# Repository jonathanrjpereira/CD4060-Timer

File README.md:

# CD4060 Timer

The timer can be set for a time delay from 15 seconds upto 24 hours.
The time delay can be easily changed to control the state of any device connected to the output.

**Order PCB:**

## Electronic Components
| Qty | Component | Buy |
| ------------- | ------------- | ------------- |
| 1 | CD4060 |[AliExpress](http://s.click.aliexpress.com/e/kyO7qcg) |
| 1 | IC Holder |[AliExpress](http://s.click.aliexpress.com/e/cHvnfsrA) |
| 1 | 7805 Voltage Regulator |[AliExpress](http://s.click.aliexpress.com/e/b1D8MbCk) |
| 1 | 10P DIP Switch |[AliExpress](http://s.click.aliexpress.com/e/bWTOIl7K) |
| 1 | BC547 PNP Transistor |[AliExpress](http://s.click.aliexpress.com/e/bpL0Irsk) |
| 12 | 1KΩ Resistor |[AliExpress](http://s.click.aliexpress.com/e/bh4eqrQs) |
| 2 | 910KΩ Resistor |[AliExpress](http://s.click.aliexpress.com/e/bh4eqrQs) |
| 1 | 3KΩ,100KΩ,1MΩ Resistor |[AliExpress](http://s.click.aliexpress.com/e/bh4eqrQs) |
| 2 | 10MΩ Resistor |[AliExpress](http://s.click.aliexpress.com/e/bQYFOHo4) |
| 1 | 22MΩ Resistor |[AliExpress](http://s.click.aliexpress.com/e/bQYFOHo4) |
| 11 | IN4004 Diode |[AliExpress](http://s.click.aliexpress.com/e/HW1fm16) |
| 1 | Tactile Momentary Push Buttons |[AliExpress](http://s.click.aliexpress.com/e/c77Ajrpq) |
| 12 | 5mm LED |[AliExpress](http://s.click.aliexpress.com/e/wuFpLXS) |
| 1 | 100uF Capacitor |[AliExpress](http://s.click.aliexpress.com/e/c9FHzl5W) |
| 1 | 0.22uF,0.3uF Capacitor |[AliExpress](http://s.click.aliexpress.com/e/byQG0DZW) |
| 2 | 0.1uF (100nF) Capacitor |[AliExpress](http://s.click.aliexpress.com/e/byQG0DZW) |
| 1 | 3 Pin Screw Terminal |[AliExpress](http://s.click.aliexpress.com/e/bj5UNUs0) |
| 1 | 5V Relay |[AliExpress](http://s.click.aliexpress.com/e/xyrHlu8) |
| 1 | SPDT Slide Switch |[AliExpress](http://s.click.aliexpress.com/e/cDjWUvjK) |
| 1 | DPDT Slide Switch |[AliExpress](http://s.click.aliexpress.com/e/bCi1v5gk) |
| 1 | 9V Battery Holder |[AliExpress](http://s.click.aliexpress.com/e/c3jbp72Y) |
| 1 | 9V Battery |[AliExpress](http://s.click.aliexpress.com/e/bbDirGHE) |
| 1 | PCB |[AliExpress](http://s.click.aliexpress.com/e/dhgwzKY) |

| Tools | Buy |
|--|--|
|Soldering Iron|[AliExpress](http://s.click.aliexpress.com/e/E83bSJI) |
|Soldering Wire|[AliExpress](http://s.click.aliexpress.com/e/PdhB0nm) |
|Mini PCB Hand Drill + Bits|[AliExpress](http://s.click.aliexpress.com/e/b93tomjI) |

## Working
**CD4060:**

The CD4060 consists of an oscillator section and 14 ripple carry binary counter stages. The oscillator configuration allows design of RC oscillator circuits. A RESET input is provided which resets the counter to the all-0's state and disables the oscillator. The counters are reset to the zero state by a logical “1” at the reset input independent of clock. The counters are advanced one count on the negative transition of each clock pulse.

**Timing Cycle:**

R2 must satisfy the following equation: 

where n is the Output Number i.e. 

where 2.2 is the internal propagation delay.

## Circuit

The Timer IC requires the external RC network to be preconfigured in order to generate proper timing oscillations. External resets may be used to reset the timer. The time selector is configured to change the RC network value. The high power appliances are turned on when the relay is activated.

**Resistor Calculation:**

The table below shows the timing cycle of each output calculated by using the formulae given above.

We can see that if we choose the value of R1 to be 1.9MΩ, we can obtain an output that varies from 14.79≈15sec to 4hr.

Similarly if we choose R1 to be 10.9MΩ, we obtain an output that varies from 1.4min to 24hr.

I wrote a small [Python script](https://github.com/jonathanrjpereira/CD4060-Timer/blob/master/time.py) to calculate the time delay for various resistance values including 1.9MΩ and 10MΩ.

As shown in the Resistor Calculation chart, we can get different time delays from the same output pins by simply changing the value of R. But we must also satisfy this equation  as explained earlier.

From this equation, we learn that if R = 1.9MΩ (1MΩ + 910KΩ), we must connect a suitable resistance of approximately 3.8MΩ-19MΩ to pin 11. Similarly if
R = 10.9MΩ (10MΩ + 910KΩ), we must connect a suitable resistance of approximately 21.8MΩ-109MΩ to pin 11. Hence we have chosen standard resistor values of 10MΩ and 22MΩ respectively.

We use a DPDT switch to toggle between these two resistor combinations. Note that the value of Cx i.e C5 is a constant 0.22uF and does not change by toggling the switch.

A 10-pin DIP switch is used to select a single output pin and connect it to the relay. Hence only when this pin goes HIGH, will the relay get activated.

C4 and R12 reset the timer when the circuit is turned ON through switch S4. The circuit can be reset (while being ON) by pressing the momentary switch S2.

The 7805 regulates the supply voltage from a 9V/12V source and LED11 indicates that the circuit is turned ON.

High power loads can be connected to the relays output terminals J1. When the relay is not activated, the Common(COM) terminal is connected to Normally Closed(NC) terminal. But when the relay is activated, the Common(COM) terminal is connected to Normally Open(NO) terminal. LED12 is used to indicate whether the relay has been activated.

Transistor T1 acts as a switch an ensures sufficient drive current is provided to the relay. Diode D11 acts as a flyback diode which protects the transistor T1 from voltage spikes caused by the relay coil.

Capacitor's C1, C2 & C3 are used to filter noise in the supply line.

You can **Order the PCB:** 

Or you can printout the [PDF file](https://github.com/jonathanrjpereira/CD4060-Timer/blob/master/img/printable.pdf) and make your own PCB using the [Iron-on method]().

## Contributing🛠
Are you an engineer or hobbyist who has a great idea for a new feature in this project? Maybe you have a good idea for a bug fix? Feel free to grab our code & schematics from Github and tinker with it. Don't forget to smash ⭐️ & the Pull Request button.

[![alt text][1.1]][1] [![alt text][2.1]][2] [![alt text][3.1]][3]

[1.1]: https://github.com/jonathanrjpereira/Social-Media-README/blob/master/youtube.png (YouTube)
[2.1]: https://github.com/jonathanrjpereira/Social-Media-README/blob/master/instagram.png (Instagram)
[3.1]: https://github.com/jonathanrjpereira/Social-Media-README/blob/master/github.png (GitHub)

[1]: https://www.youtube.com/channel/UCRW-41O1vy98KKgJRQoYzdg
[2]: https://www.instagram.com/electroguruji/
[3]: https://github.com/jonathanrjpereira

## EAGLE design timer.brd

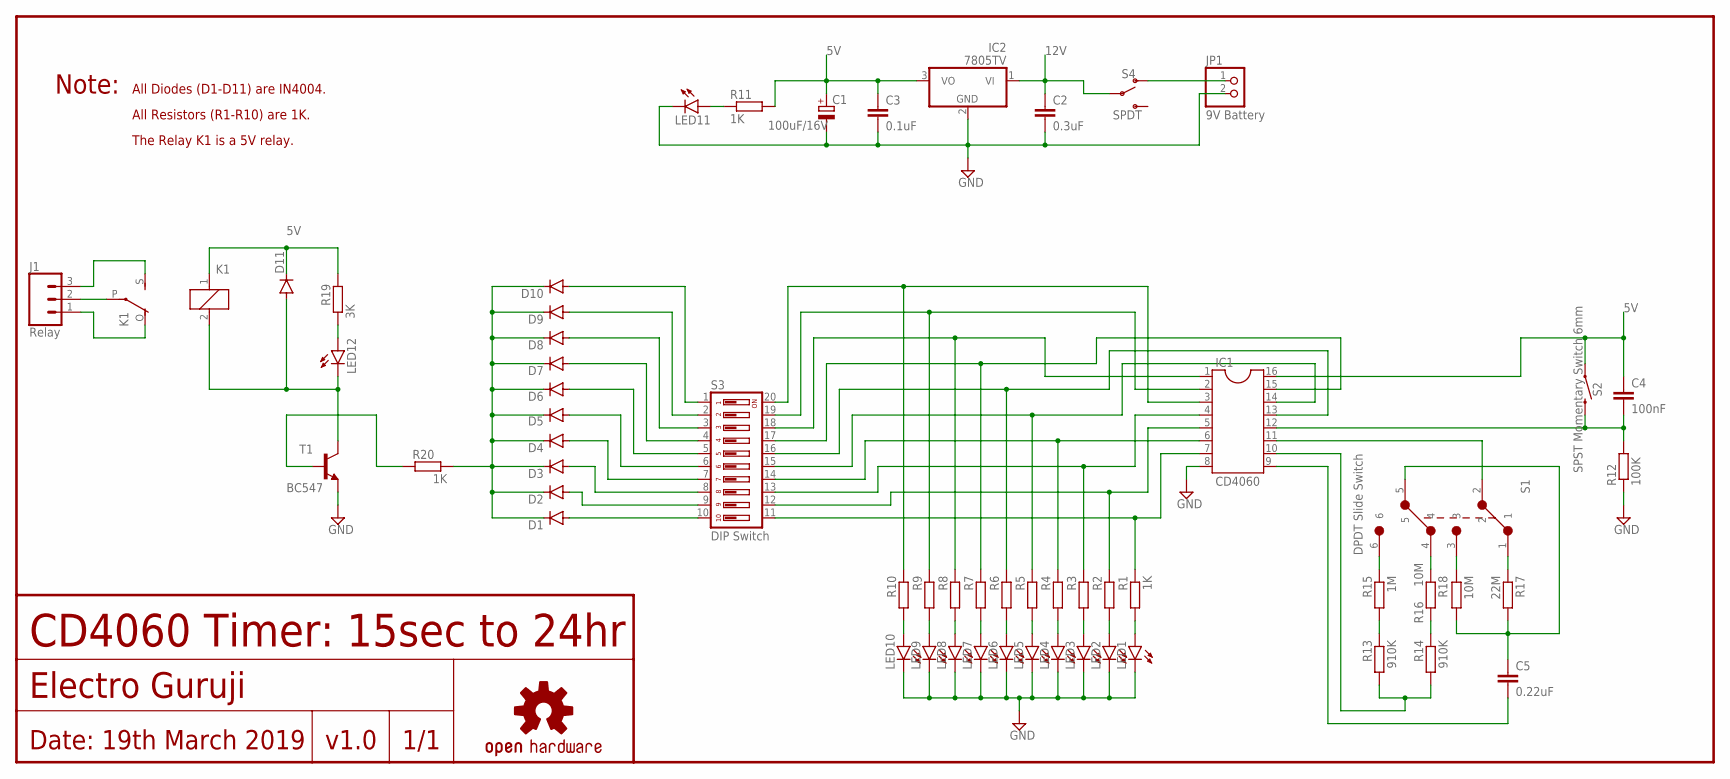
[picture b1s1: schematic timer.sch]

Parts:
C1: 100uF/16V; E2,5-6
C2: 0.3uF; C025-050X050
C3: 0.1uF; C025-050X050
C4: 100nF; C025-050X050
C5: 0.22uF; C102-043X133
D1, D2, D3, D4, D5, D6, D7, D8, D9, D10, D11: 1N4004; DO41-10
IC1: CD4060; SOCKET-16
IC2: 7805TV; TO220V
J1: Relay; SCREWTERMINAL-5MM-3
JP1: 9V Battery; 1X02
K1: 5V; ZF112
LED1, LED2, LED3, LED4, LED5, LED6, LED7, LED8, LED9, LED10, LED11, LED12: LED5MM
LOGO1: OSHW-LOGOS-COPPER; OSHW-LOGO-S_COPPER
R1, R11, R20: 1K; 0207/10
R2, R3, R4, R5, R6, R7, R8, R9, R10: R-EU_0207/10; 0207/10
R12: 100K; 0207/10
R13, R14: 910K; 0207/10
R15: 1M; 0207/10
R16, R18: 10M; 0207/10
R17: 22M; 0207/10
R19: 3K; 0207/10
S1: DPDT Slide Switch; DPDT_SEC
S2: SPST Momentary Switch 6mm; TACTILE_SWITCH_PTH_6.0MM
S3: DIP Switch; DIP10YL
S4: SPDT; SWITCH_SPDT_PTH_11.6X4.0MM
T1: BC547; TO92-EBC

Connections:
5V: C1.+, C3.1, C4.1, D11.C, IC1.16, IC2.3 (VO), K1.1, R11.2, R19.2, S2.1
12V: C2.1, IC2.1 (VI), S4.2
GND: C1.-, C2.2, C3.2, IC1.8, IC2.2 (GND), JP1.2, LED1.K (C), LED2.K (C), LED3.K (C), LED4.K (C), LED5.K (C), LED6.K (C), LED7.K (C), LED8.K (C), LED9.K (C), LED10.K (C), LED11.K (C), R12.1, T1.E
unnamed: C4.2, IC1.12, R12.2, S2.3 (2)
unnamed: LED11.A, R11.1
unnamed: IC1.10, R13.2, R14.2
unnamed: IC1.7, R1.1, S3.11
unnamed: R13.1, R15.2
unnamed: R14.1, R16.2
unnamed: C5.1, R17.2, R18.2, S1.5
unnamed: R18.1, S1.3
unnamed: R17.1, S1.1
unnamed: R16.1, S1.4
unnamed: R15.1, S1.6
unnamed: IC1.11, S1.2
unnamed: C5.2, IC1.9
unnamed: D1.A, S3.10
unnamed: IC1.5, R2.1, S3.12
unnamed: IC1.4, R3.1, S3.13
unnamed: IC1.6, R4.1, S3.14
unnamed: IC1.14, R5.1, S3.15
unnamed: IC1.13, R6.1, S3.16
unnamed: IC1.15, R7.1, S3.17
unnamed: IC1.1, R8.1, S3.18
unnamed: IC1.2, R9.1, S3.19
unnamed: IC1.3, R10.1, S3.20
unnamed: D2.A, S3.9
unnamed: D3.A, S3.8
unnamed: D4.A, S3.7
unnamed: D5.A, S3.6
unnamed: D6.A, S3.5
unnamed: D7.A, S3.4
unnamed: D8.A, S3.3
unnamed: D9.A, S3.2
unnamed: D10.A, S3.1
unnamed: LED10.A, R10.2
unnamed: LED9.A, R9.2
unnamed: LED8.A, R8.2
unnamed: LED7.A, R7.2
unnamed: LED6.A, R6.2
unnamed: LED5.A, R5.2
unnamed: LED4.A, R4.2
unnamed: LED3.A, R3.2
unnamed: LED2.A, R2.2
unnamed: LED1.A, R1.2
unnamed: R20.2, T1.B
unnamed: D11.A, K1.2, LED12.K (C), T1.C
unnamed: LED12.A, R19.1
unnamed: J1.2, K1.P
unnamed: J1.3, K1.S
unnamed: J1.1, K1.O
unnamed: JP1.1, S4.1 (O)
unnamed: D1.C, D2.C, D3.C, D4.C, D5.C, D6.C, D7.C, D8.C, D9.C, D10.C, R20.1

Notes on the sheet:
Note:
All Diodes (D1-D11) are IN4004.
All Resistors (R1-R10) are 1K.
The Relay K1 is a 5V relay.
CD4060 Timer: 15sec to 24hr
Electro Guruji
Date: 19th March 2019
v1.0
1/1

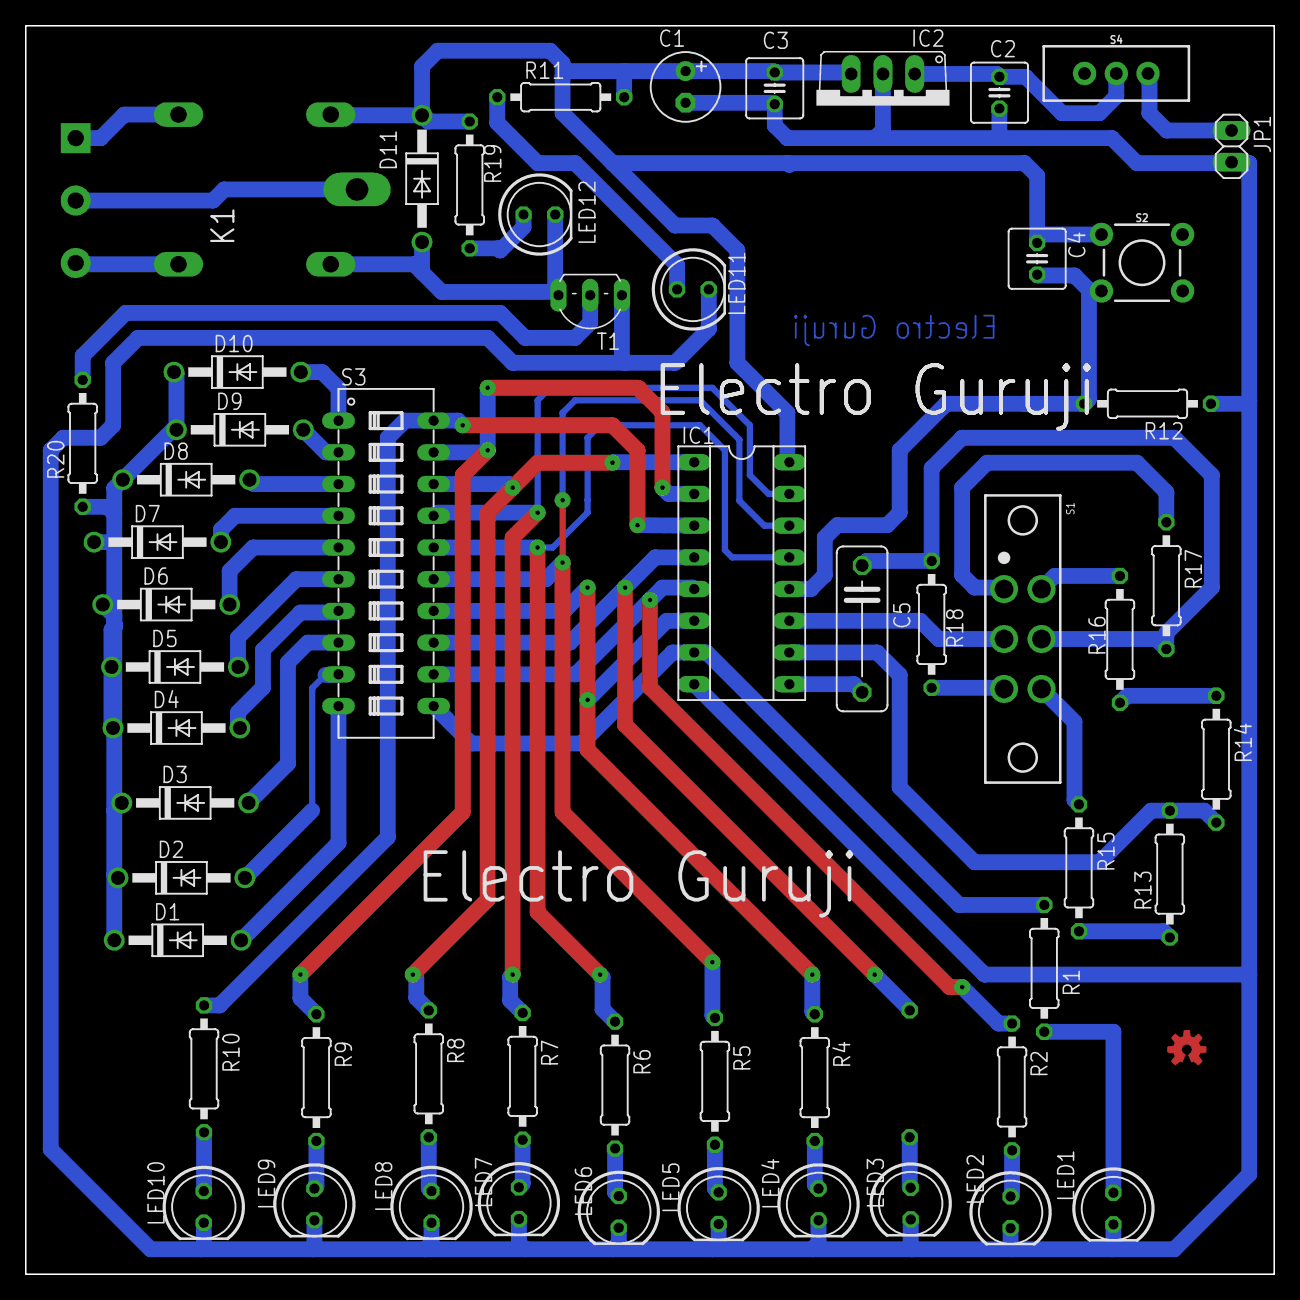
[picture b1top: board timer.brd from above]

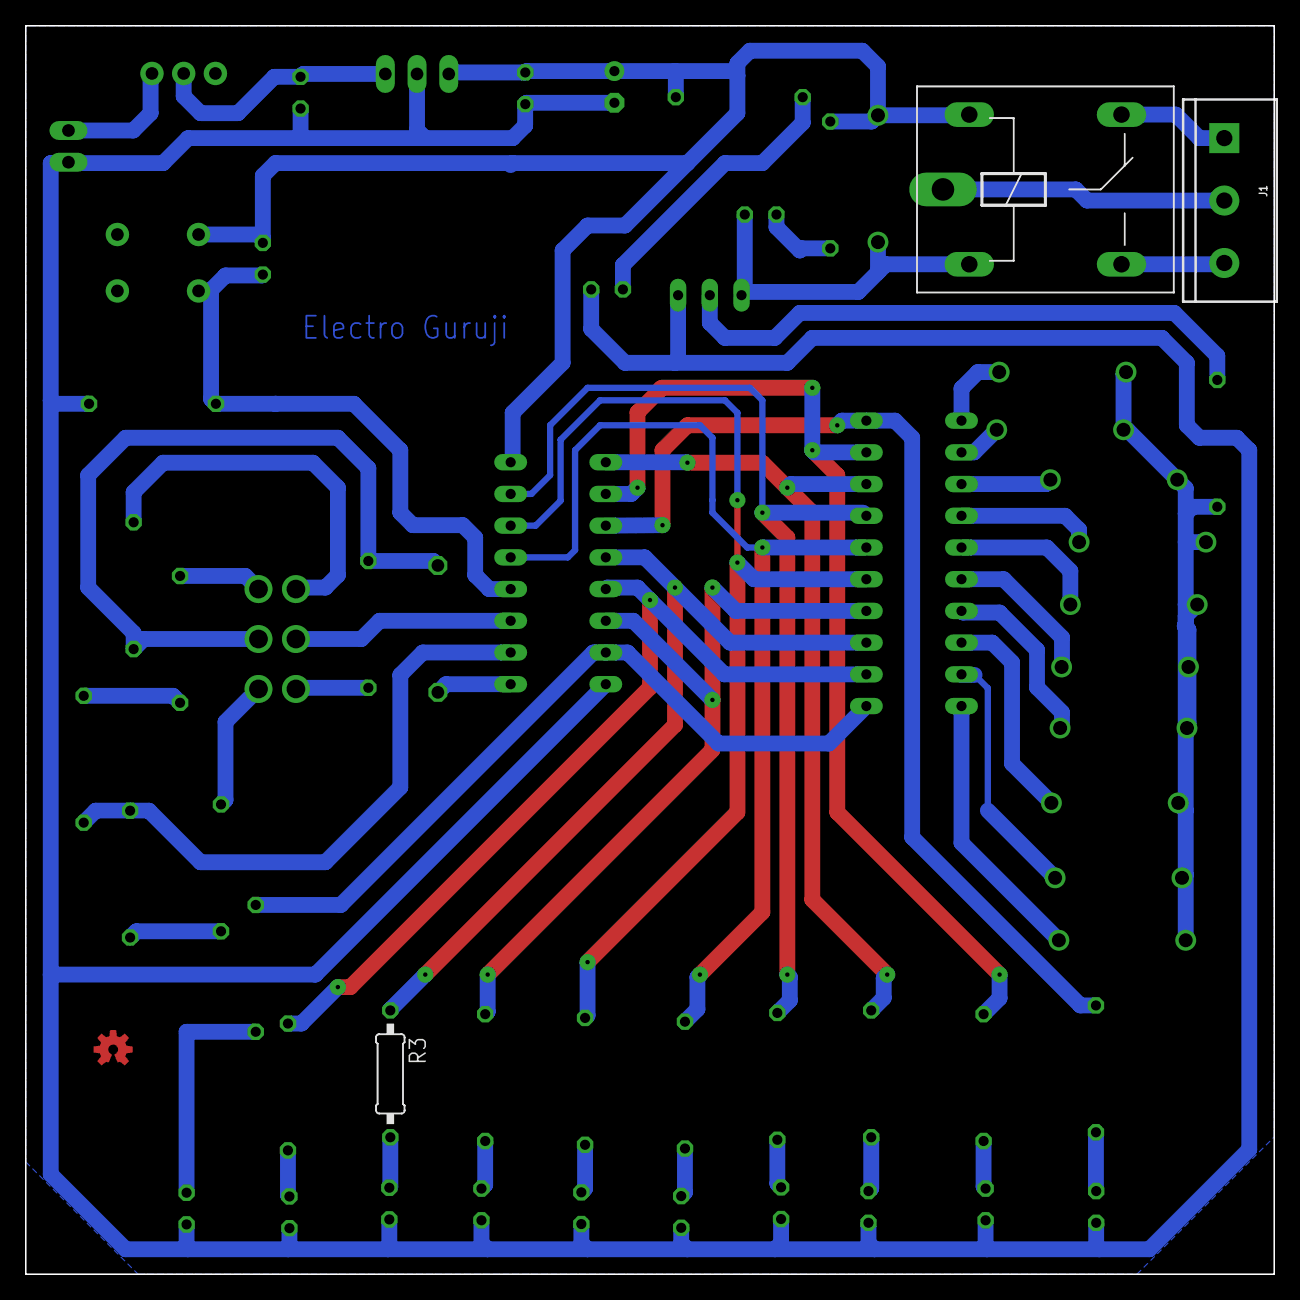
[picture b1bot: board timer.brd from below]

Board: 2 copper layers, 100.0 x 100.0 mm, 59 parts (3 on the bottom side), 53 nets.

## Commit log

2019-03-17 Calculate Output times
2019-03-19 Board
2019-03-19 Schematic
2019-03-19 Output Timing Calculator
2019-03-19 Printable
2019-03-19 Eagle
2019-03-20 Added Values
2019-03-20 Values + OS Logo + Titlesheet
2019-03-20 graphics
2019-03-20 Resistor Calculation
2019-03-20 Working + Circuit
2019-03-20 Changed Relay Output Connector
    Pinhead JP2 changed to screw terminal J1
2019-03-20 Added values of R13,R14
    910K Ohm
2019-03-20 Component BOM
2019-03-20 Mega Ohm BOM

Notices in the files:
parts and their libraries:
SparkFun-Switches: Licensing: Creative Commons ShareAlike 4.0 International - https://creativecommons.org/licenses/by-sa/4.0
